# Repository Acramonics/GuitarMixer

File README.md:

AEGM: Acoustic/Electric Guitar Mixer
====================================

**Andrew Martin (c) 2025 - 2026**

**Still not working properly yet**

**V1.3 has switched to a dual rail power supply to save the effort of
  biasing all the op amp inputs. Awaiting the new boards**

*AEGM* is designed as a simple 2-channel mixer for guitars like the
PRS range that have both acoustic (piezo) and coil pickups. The
guitars have a combined output, but it doesn't work that well since
the piezo output needs a higher impedance than a standard guitar amp
to work well and your options for balancing the volumes are limited.
Also, you cannot use a pedal on the coil output without also putting
it on the piezo output.

The guitar gives you the option of using two separate outputs which is
fine if you have two amps, but this little mixer is designed to allow
you to use the two outputs separately and then send them to a single
amp.

**V1.2 was simulated in KiCad-Spice and appeared to be working
  properly, but when built was overlayed with noise and distorted.**

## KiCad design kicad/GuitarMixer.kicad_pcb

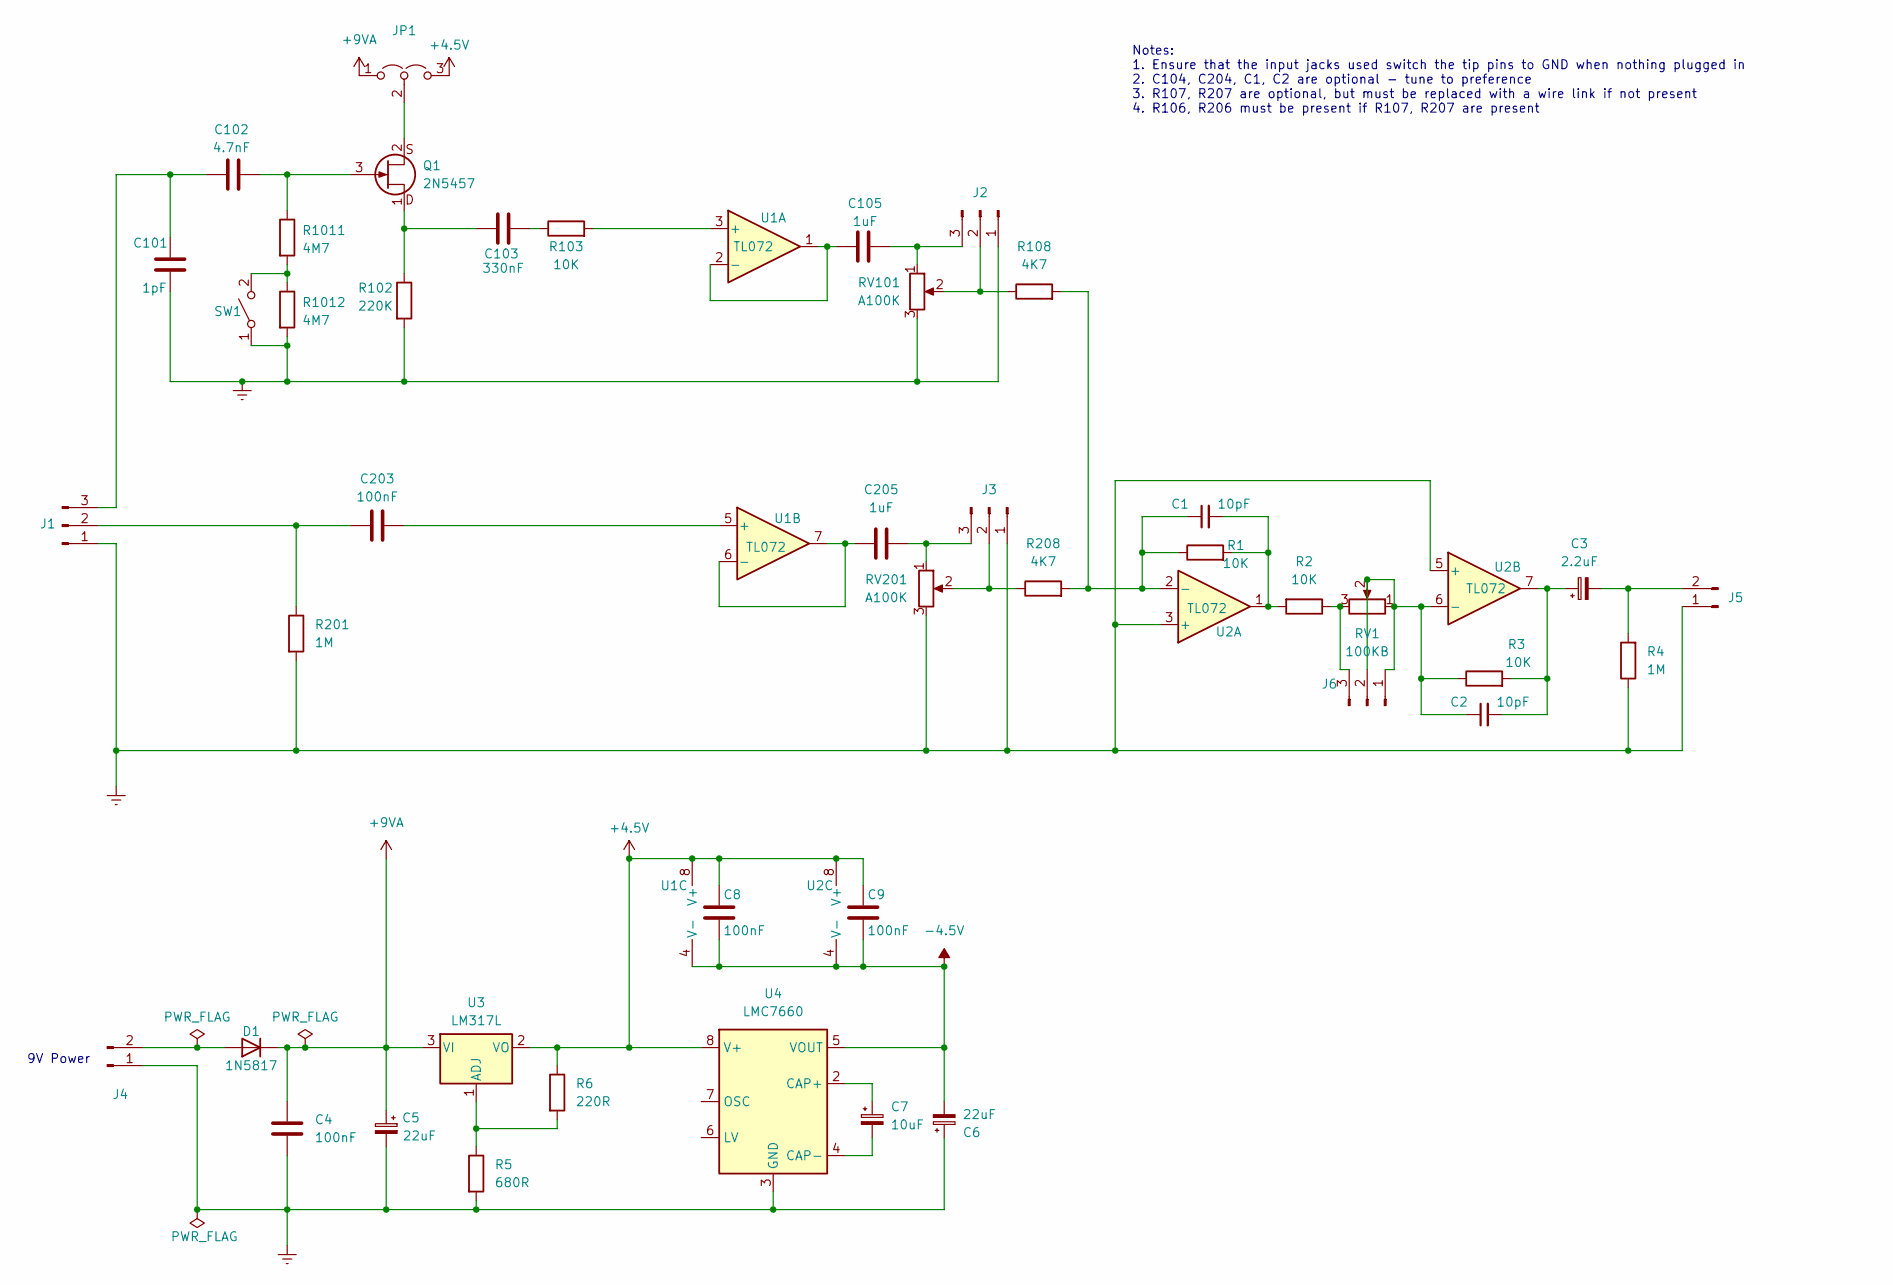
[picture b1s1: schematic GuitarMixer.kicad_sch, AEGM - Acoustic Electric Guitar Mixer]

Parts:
C1, C2: 10pF; C_Disc_D4.3mm_W1.9mm_P5.00mm
C3: 2.2uF; CP_Radial_D5.0mm_P2.00mm
C4, C8, C9: 100nF; C_Rect_L7.0mm_W3.5mm_P5.00mm
C5, C6: 22uF; CP_Radial_D5.0mm_P2.00mm
C7: 10uF; CP_Radial_D5.0mm_P2.00mm
C101: 1pF; C_Disc_D4.3mm_W1.9mm_P5.00mm
C102: 4.7nF; C_Rect_L7.2mm_W2.5mm_P5.00mm_FKS2_FKP2_MKS2_MKP2
C103: 330nF; C_Rect_L7.2mm_W2.5mm_P5.00mm_FKS2_FKP2_MKS2_MKP2
C105, C205: 1uF; C_Rect_L7.2mm_W4.5mm_P5.00mm_FKS2_FKP2_MKS2_MKP2
C203: 100nF; C_Rect_L7.2mm_W2.5mm_P5.00mm_FKS2_FKP2_MKS2_MKP2
D1: 1N5817; D_DO-35_SOD27_P7.62mm_Horizontal
J1, J2, J3, J6: Conn_01x03_Pin; Molex_KK-254_AE-6410-03A_1x03_P2.54mm_Vertical
J4, J5: Conn_01x02_Pin; Molex_KK-254_AE-6410-02A_1x02_P2.54mm_Vertical
JP1: Jumper_3_Open; SolderJumper-3_P1.3mm_Open_Pad1.0x1.5mm
Q1: 2N5457; TO-92_HandSolder
R1, R2, R3, R103: 10K; R_Axial_DIN0207_L6.3mm_D2.5mm_P10.16mm_Horizontal
R4, R201: 1M; R_Axial_DIN0207_L6.3mm_D2.5mm_P10.16mm_Horizontal
R5: 680R; R_Axial_DIN0207_L6.3mm_D2.5mm_P2.54mm_Vertical
R6: 220R; R_Axial_DIN0207_L6.3mm_D2.5mm_P2.54mm_Vertical
R102: 220K; R_Axial_DIN0207_L6.3mm_D2.5mm_P10.16mm_Horizontal
R108, R208: 4K7; R_Axial_DIN0207_L6.3mm_D2.5mm_P2.54mm_Vertical
R1011, R1012: 4M7; R_Axial_DIN0207_L6.3mm_D2.5mm_P10.16mm_Horizontal
RV1: 100KB
RV101, RV201: A100K
SW1: SW_SPST; SPDT_SlideSwitch
U1, U2: TL072; DIP-8_W7.62mm
U3: LM317L; TO-92_HandSolder
U4: LMC7660; DIP-8_W7.62mm

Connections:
+4.5V: C8.1, C9.1, JP1.3 (B), R6.1, U1.8 (V+), U2.8 (V+), U3.2 (VO), U4.8 (V+)
+9VA: C4.1, C5.1, D1.1 (K), JP1.1 (A), U3.3 (VI)
-4.5V: C6.2, C8.2, C9.2, U1.4 (V-), U2.4 (V-), U4.5 (VOUT)
Earth: C4.2, C5.2, C6.1, C101.2, J1.1, J2.1, J3.1, J4.1, J5.1, R4.1, R5.2, R102.2, R201.2, R1012.2, RV101.3, RV201.3, SW1.1 (A), U2.3 (+), U2.5 (+), U4.3 (GND)
unnamed: C1.2, R1.2, R2.2, U2.1
unnamed: C2.2, C3.1, R3.2, U2.7
unnamed: C103.2, R103.1
unnamed: D1.2 (A), J4.2
unnamed: C203.1, J1.2, R201.1
unnamed: C101.1, C102.1, J1.3
unnamed: J2.2, R108.1, RV101.2
unnamed: C105.2, J2.3, RV101.1
unnamed: J3.2, R208.1, RV201.2
unnamed: C205.2, J3.3, RV201.1
unnamed: C3.2, J5.2, R4.2
unnamed: C2.1, J6.1, J6.2, R3.1, RV1.1, RV1.2, U2.6 (-)
unnamed: J6.3, R2.1, RV1.3
unnamed: JP1.2 (C), Q1.2 (D)
unnamed: C102.2, Q1.3 (G), R1011.1
unnamed: C103.1, Q1.1 (S), R102.1
unnamed: R1011.2, R1012.1, SW1.2 (B)
unnamed: R103.2, U1.3 (+)
unnamed: C105.1, U1.1, U1.2 (-)
unnamed: C203.2, U1.5 (+)
unnamed: C205.1, U1.6 (-), U1.7
unnamed: C1.1, R1.1, R108.2, R208.2, U2.2 (-)
unnamed: R5.1, R6.2, U3.1 (ADJ)
unnamed: C7.1, U4.2 (CAP+)
unnamed: C7.2, U4.4 (CAP-)

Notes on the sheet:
9V Power
Notes: 1. Ensure that the input jacks used switch the tip pins to GND when nothing plugged in 2. C104, C204, C1, C2 are optional - tune to preference 3. R107, R207 are optional, but must be replaced with a wire link if not present 4. R106, R206 must be present if R107, R207 are present

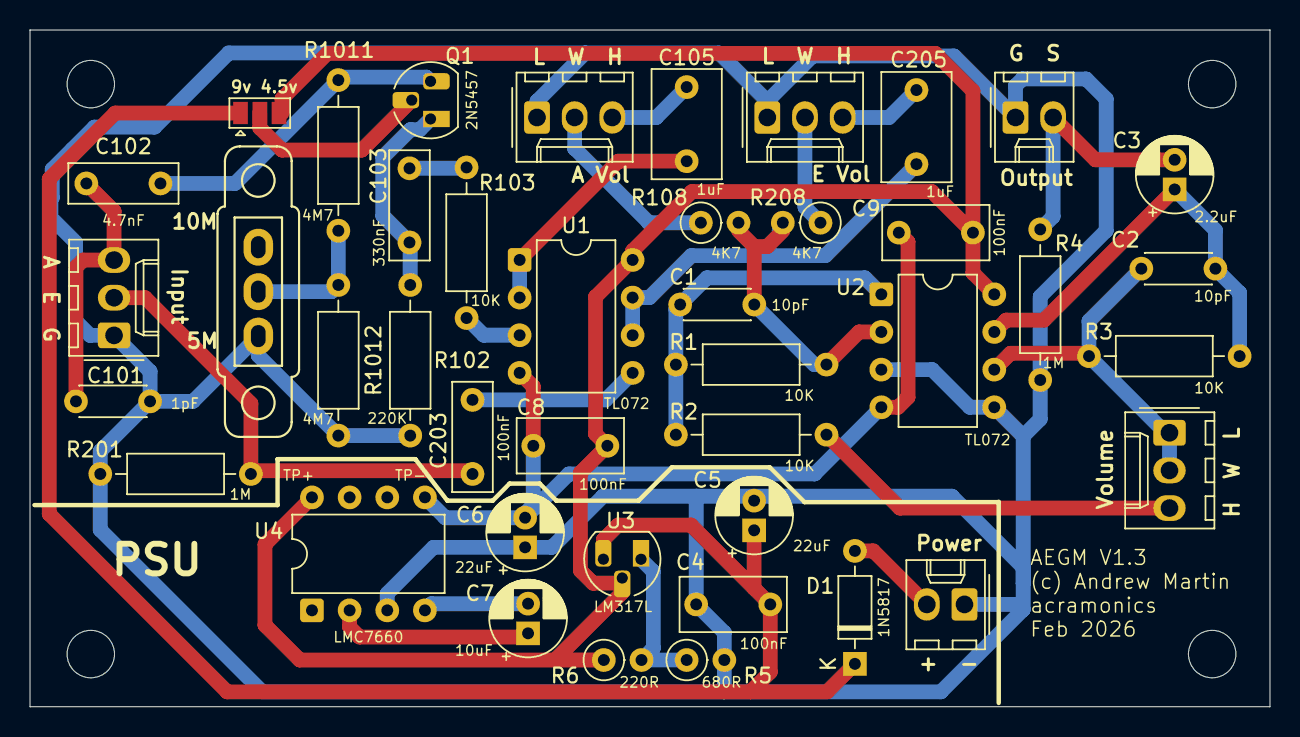
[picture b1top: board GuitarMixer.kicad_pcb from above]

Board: 2 copper layers, 83.7 x 45.6 mm, 42 parts (0 on the bottom side), 29 nets.

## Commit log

2025-09-08 Initial Commit V0.2
2025-09-08 Removed redundant files
2025-09-08 Added README.md and inspiration directory
2025-09-08 Fixed slide switch and changed trimmer to pot connection
2025-09-08 Updated gerber files
2025-09-10 Added notes on how to fix problems and some more inspiration files
2025-09-10 Moved stuff around for separate earth
2025-09-11 Finished test board with lots of options for playing with values
2025-09-12 Added PDFs for V0.2
2025-10-08 Added PCB PDF
2025-10-08 Added PDF
2025-10-09 Update to project file
2025-10-10 V1.0
2025-10-17 Redid the feedback on the non-inverting amplifier for electric guitar
2026-01-12 Added simulation and updated schematic to V1.2 based on simulation
2026-01-13 Board created
2026-01-13 Fixed swapped labels
2026-01-13 Added PDF files and BOM
2026-02-25 Updated BOM
2026-02-26 New version with split rail power supply
2026-02-26 Moved the voltage setting resistors and created gerber and distribution files
